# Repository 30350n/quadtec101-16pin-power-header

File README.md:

# quadtec101
A Quad Panning Oscillator designed for the Neuztec 4 Festival

**This is a modified version of the quadtec101, which makes use of the 16pin eurorack header for +5V power distribution.
To fit the bigger power header, I removed the original battery circuit, so this version won't work as a standalone module anymore.**

More info here: [cctv.fm](https://www.cctv.fm/product-page/quadtec-101)

Sign up here: [Neuzlab](http://www.neuztec.ca/neuzlab/)

>QUADTEC-101 A MUSICAL INSTRUMENT FROM THE FUTURE.

>THE GARDEN CITY ELECTRONIC MUSIC COMMUNITY CREATED A TIMEMACHINE USING RARE TELSA BLUEPRINTS AND WENT INTO THE FUTURE TO GATHER DATA OF THE DAY; SEEKING OUT INSTRUMENTS FROM THE CREATIVE YOUTH OF THE FUTURE. UPON RETURNING TO 2019 THEY BROUGHT THOSE IDEAS TO FILIP PIETRUSZEWSKI TO RE-ENGINEER, DESIGN, AND REALIZE THIS FUTURISTIC INSTRUMENT USING MODERN AND ANTIIQUE TOOLS AT HIS MAD SCIENCE LAB AT CAPITAL CITY TRANSISTOR AND VALVE.

# Licensing

CC BY-NC-SA

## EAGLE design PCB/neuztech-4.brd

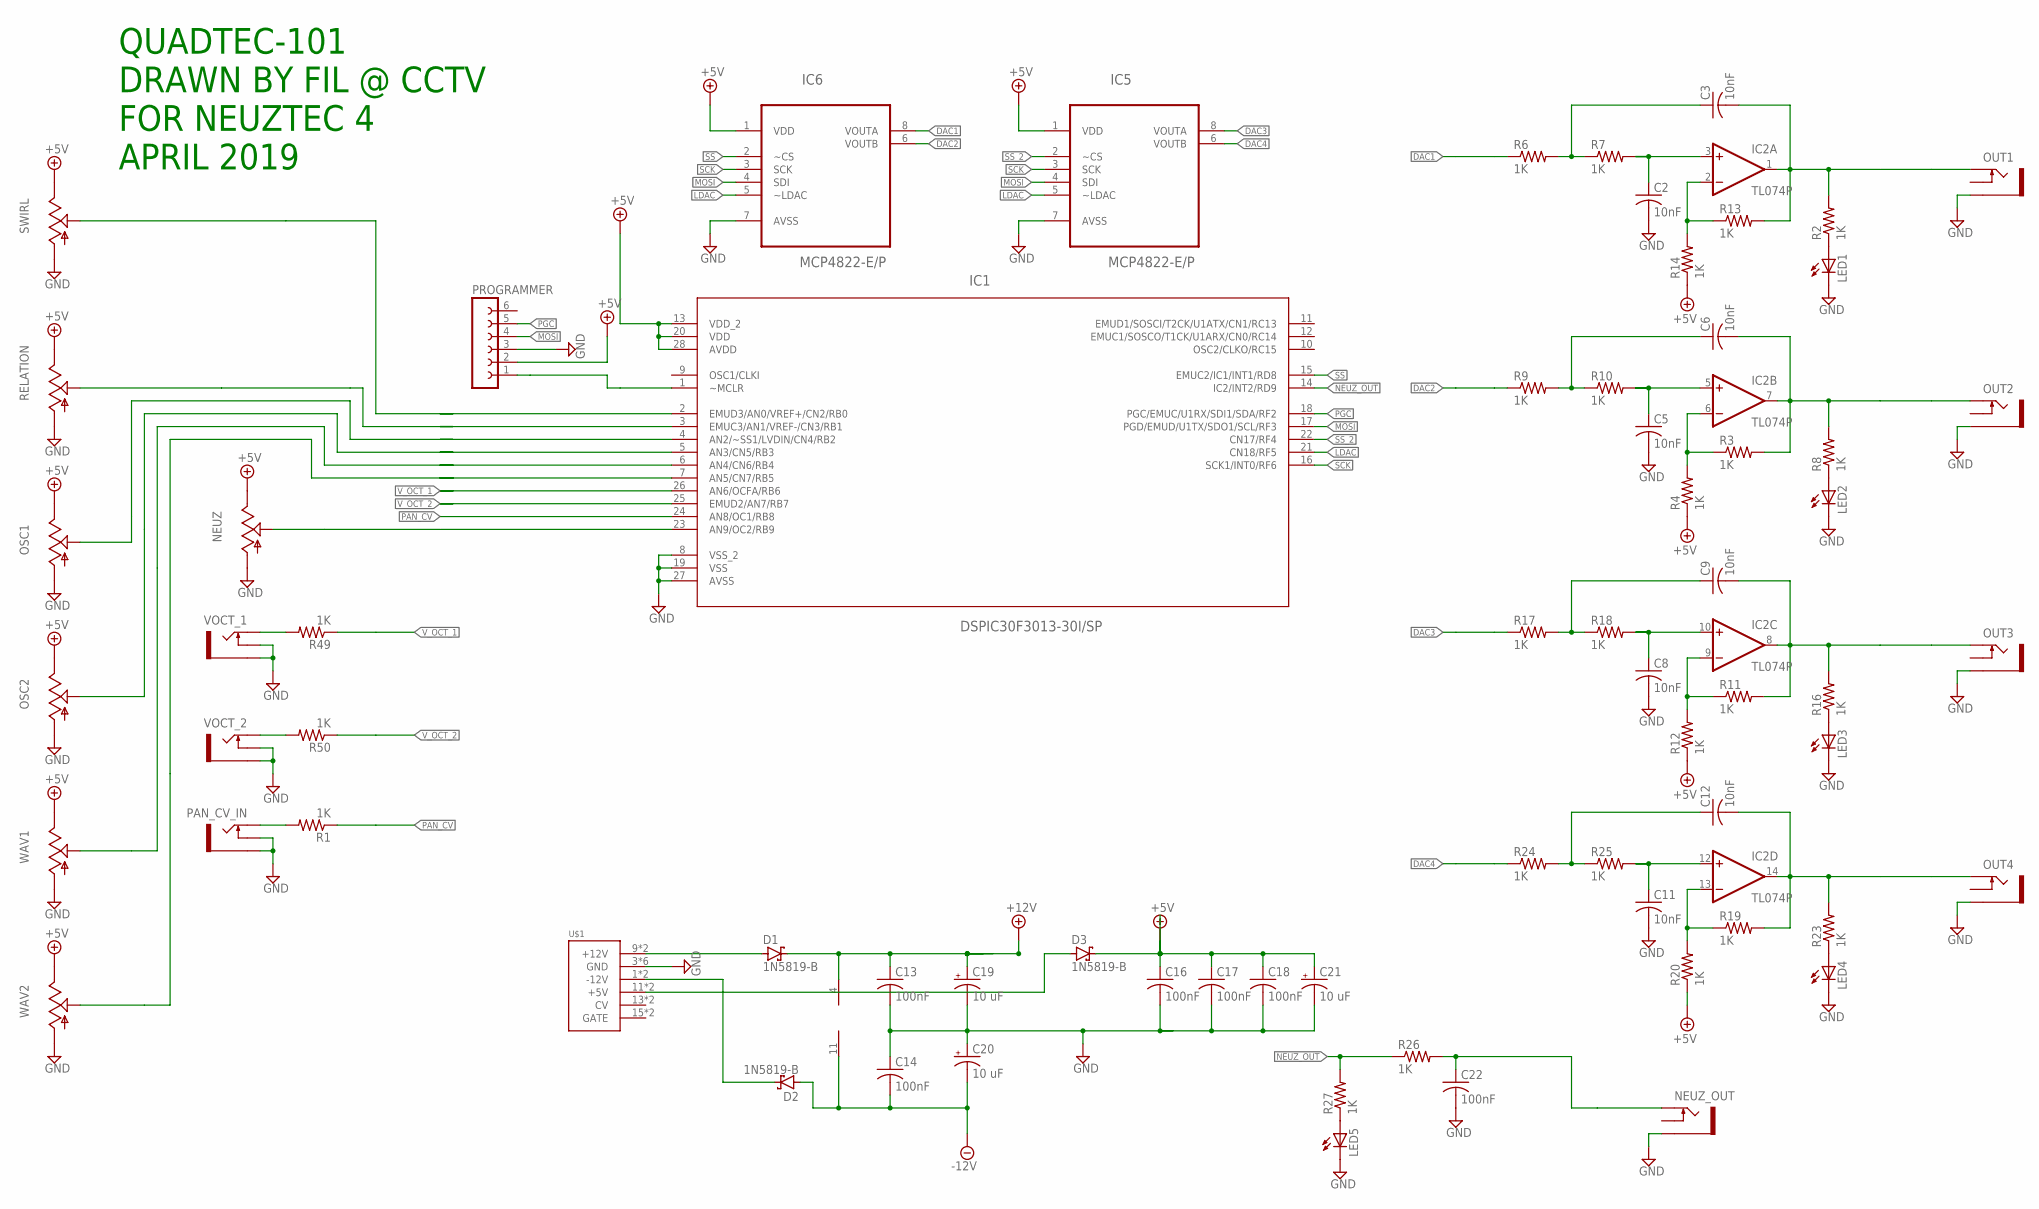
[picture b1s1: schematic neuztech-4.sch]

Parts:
C2, C3, C5, C6, C8, C9, C11, C12: 10nF; C050-035X075
C13, C14, C16, C17, C18, C22: 100nF; C050-024X044
C19, C20, C21: 10 uF; E2-4
D1, D2, D3: 1N5819-B; DO41-7.6
IC1: DSPIC30F3013-30I/SP; DIP254P762X508-28
IC2: TL074P; DIL14
IC5, IC6: MCP4822-E/P; DIP254P762X432-8
LED1, LED2, LED3, LED4, LED5: LED3MM
NEUZ: 9MM_SNAP-IN_POT_; 9MM_SNAP-IN_POT
NEUZ_OUT: THONKICONNNEW; WQP-PJ301M-12_JACK
OSC1, OSC2: 9MM_SNAP-IN_POT_; 9MM_SNAP-IN_POT
OUT1, OUT2, OUT3, OUT4: THONKICONNNEW; WQP-PJ301M-12_JACK
PAN_CV_IN: THONKICONNNEW; WQP-PJ301M-12_JACK
PROGRAMMER: FE06-1; FE06
R1, R2, R3, R4, R6, R7, R8, R9, R10, R11, R12, R13, R14, R16, R17, R18, R19, R20, R23, R24, R25, R26, R27, R49, R50: 1K; 0207/10
RELATION: 9MM_SNAP-IN_POT_; 9MM_SNAP-IN_POT
SWIRL: 9MM_SNAP-IN_POT_; 9MM_SNAP-IN_POT
U$1: POWER; POWER_16
VOCT_1, VOCT_2: THONKICONNNEW; WQP-PJ301M-12_JACK
WAV1, WAV2: 9MM_SNAP-IN_POT_; 9MM_SNAP-IN_POT

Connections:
+5V: C16.1, C17.1, C18.1, C21.+, D3.C, IC1.13 (VDD_2), IC1.20 (VDD), IC1.28 (AVDD), IC5.1 (VDD), IC6.1 (VDD), NEUZ.3 (E), OSC1.3 (E), OSC2.3 (E), PROGRAMMER.2, R4.1, R12.1, R14.1, R20.1, RELATION.3 (E), SWIRL.3 (E), WAV1.3 (E), WAV2.3 (E)
+12V: C13.1, C19.+, D1.C, IC2.4 (V+)
-12V: C14.2, C20.-, D2.A, IC2.11 (V-)
DAC1: IC6.8 (VOUTA), R6.1
DAC2: IC6.6 (VOUTB), R9.1
DAC3: IC5.8 (VOUTA), R17.1
DAC4: IC5.6 (VOUTB), R24.1
GND: C2.2, C5.2, C8.2, C11.2, C13.2, C14.1, C16.2, C17.2, C18.2, C19.-, C20.+, C21.-, C22.2, IC1.8 (VSS_2), IC1.19 (VSS), IC1.27 (AVSS), IC5.7 (AVSS), IC6.7 (AVSS), LED1.K (C), LED2.K (C), LED3.K (C), LED4.K (C), LED5.K (C), NEUZ.1 (A), NEUZ_OUT.P$3_SLEEVE (SLEEVE), OSC1.1 (A), OSC2.1 (A), OUT1.P$3_SLEEVE (SLEEVE), OUT2.P$3_SLEEVE (SLEEVE), OUT3.P$3_SLEEVE (SLEEVE), OUT4.P$3_SLEEVE (SLEEVE), PAN_CV_IN.P$2_SWITCH (SWITCH), PAN_CV_IN.P$3_SLEEVE (SLEEVE), PROGRAMMER.3, RELATION.1 (A), SWIRL.1 (A), U$1.3 (GND), U$1.4 (GND), U$1.5 (GND), U$1.6 (GND), U$1.7 (GND), U$1.8 (GND), VOCT_1.P$2_SWITCH (SWITCH), VOCT_1.P$3_SLEEVE (SLEEVE), VOCT_2.P$2_SWITCH (SWITCH), VOCT_2.P$3_SLEEVE (SLEEVE), WAV1.1 (A), WAV2.1 (A)
LDAC: IC1.21 (CN18/RF5), IC5.5 (~LDAC), IC6.5 (~LDAC)
MOSI: IC1.17 (PGD/EMUD/U1TX/SDO1/SCL/RF3), IC5.4 (SDI), IC6.4 (SDI), PROGRAMMER.4
unnamed: PAN_CV_IN.P$1_TIP (TIP), R1.2
unnamed: IC1.1 (~MCLR), PROGRAMMER.1
unnamed: C3.2, IC2.1 (OUT), OUT1.P$1_TIP (TIP), R2.2, R13.2
unnamed: LED1.A, R2.1
unnamed: C6.2, IC2.7 (OUT), OUT2.P$1_TIP (TIP), R3.2, R8.2
unnamed: IC2.6 (-IN), R3.1, R4.2
unnamed: C5.1, IC2.5 (+IN), R10.2
unnamed: D3.A, U$1.11 (+5V), U$1.12 (+5V)
unnamed: C3.1, R6.2, R7.1
unnamed: LED2.A, R8.1
unnamed: C6.1, R9.2, R10.1
unnamed: D2.C, U$1.1 (-12V), U$1.2 (-12V)
unnamed: C9.2, IC2.8 (OUT), OUT3.P$1_TIP (TIP), R11.2, R16.2
unnamed: IC2.9 (-IN), R11.1, R12.2
unnamed: C8.1, IC2.10 (+IN), R18.2
unnamed: LED3.A, R16.1
unnamed: IC2.2 (-IN), R13.1, R14.2
unnamed: C9.1, R17.2, R18.1
unnamed: D1.A, U$1.9 (+12V), U$1.10 (+12V)
unnamed: C12.2, IC2.14 (OUT), OUT4.P$1_TIP (TIP), R19.2, R23.2
unnamed: IC2.13 (-IN), R19.1, R20.2
unnamed: C11.1, IC2.12 (+IN), R25.2
unnamed: C2.1, IC2.3 (+IN), R7.2
unnamed: LED4.A, R23.1
unnamed: C12.1, R24.2, R25.1
unnamed: LED5.A, R27.1
unnamed: C22.1, NEUZ_OUT.P$1_TIP (TIP), R26.2
unnamed: IC1.3 (EMUC3/AN1/VREF-/CN3/RB1), RELATION.2 (S)
unnamed: IC1.4 (AN2/~SS1/LVDIN/CN4/RB2), OSC1.2 (S)
unnamed: IC1.5 (AN3/CN5/RB3), OSC2.2 (S)
unnamed: IC1.6 (AN4/CN6/RB4), WAV1.2 (S)
unnamed: IC1.7 (AN5/CN7/RB5), WAV2.2 (S)
unnamed: IC1.2 (EMUD3/AN0/VREF+/CN2/RB0), SWIRL.2 (S)
unnamed: R50.2, VOCT_2.P$1_TIP (TIP)
unnamed: R49.2, VOCT_1.P$1_TIP (TIP)
NEUZ_OUT: IC1.14 (IC2/INT2/RD9), R26.1, R27.2
NEUZ_POT: IC1.23 (AN9/OC2/RB9), NEUZ.2 (S)
PAN_CV: IC1.24 (AN8/OC1/RB8), R1.1
PGC: IC1.18 (PGC/EMUC/U1RX/SDI1/SDA/RF2), PROGRAMMER.5
SCK: IC1.16 (SCK1/INT0/RF6), IC5.3 (SCK), IC6.3 (SCK)
SS: IC1.15 (EMUC2/IC1/INT1/RD8), IC6.2 (~CS)
SS_2: IC1.22 (CN17/RF4), IC5.2 (~CS)
V_OCT_1: IC1.26 (AN6/OCFA/RB6), R49.1
V_OCT_2: IC1.25 (EMUD2/AN7/RB7), R50.1

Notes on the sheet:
QUADTEC-101 DRAWN BY FIL @ CCTV FOR NEUZTEC 4 APRIL 2019

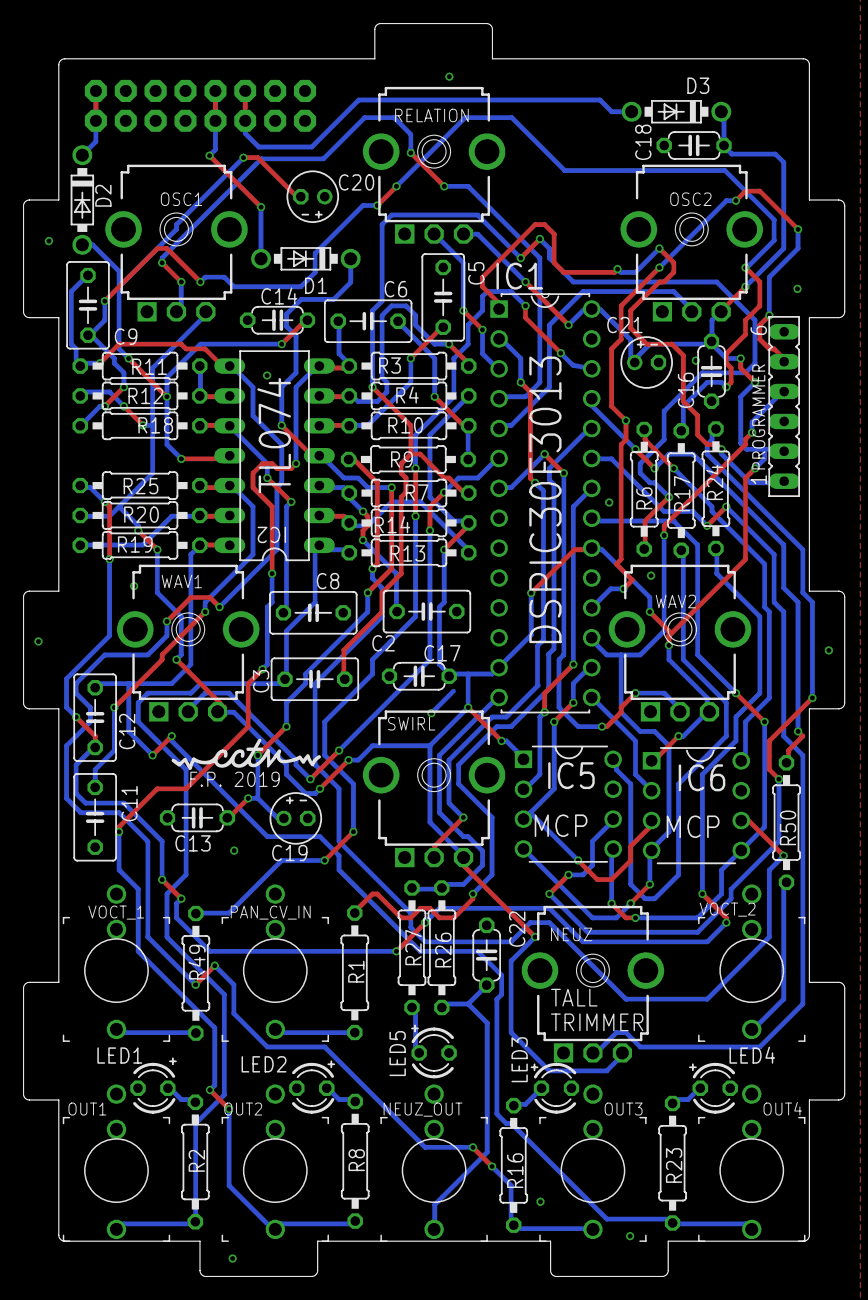
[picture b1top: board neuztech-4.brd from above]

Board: 2 copper layers, 69.8 x 106.5 mm, 71 parts (1 on the bottom side), 54 nets.

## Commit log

2020-12-12 Add 16 pin header, remove battery power distribution
2020-12-12 Rearrange components, Generate new gerbers, Update readme
